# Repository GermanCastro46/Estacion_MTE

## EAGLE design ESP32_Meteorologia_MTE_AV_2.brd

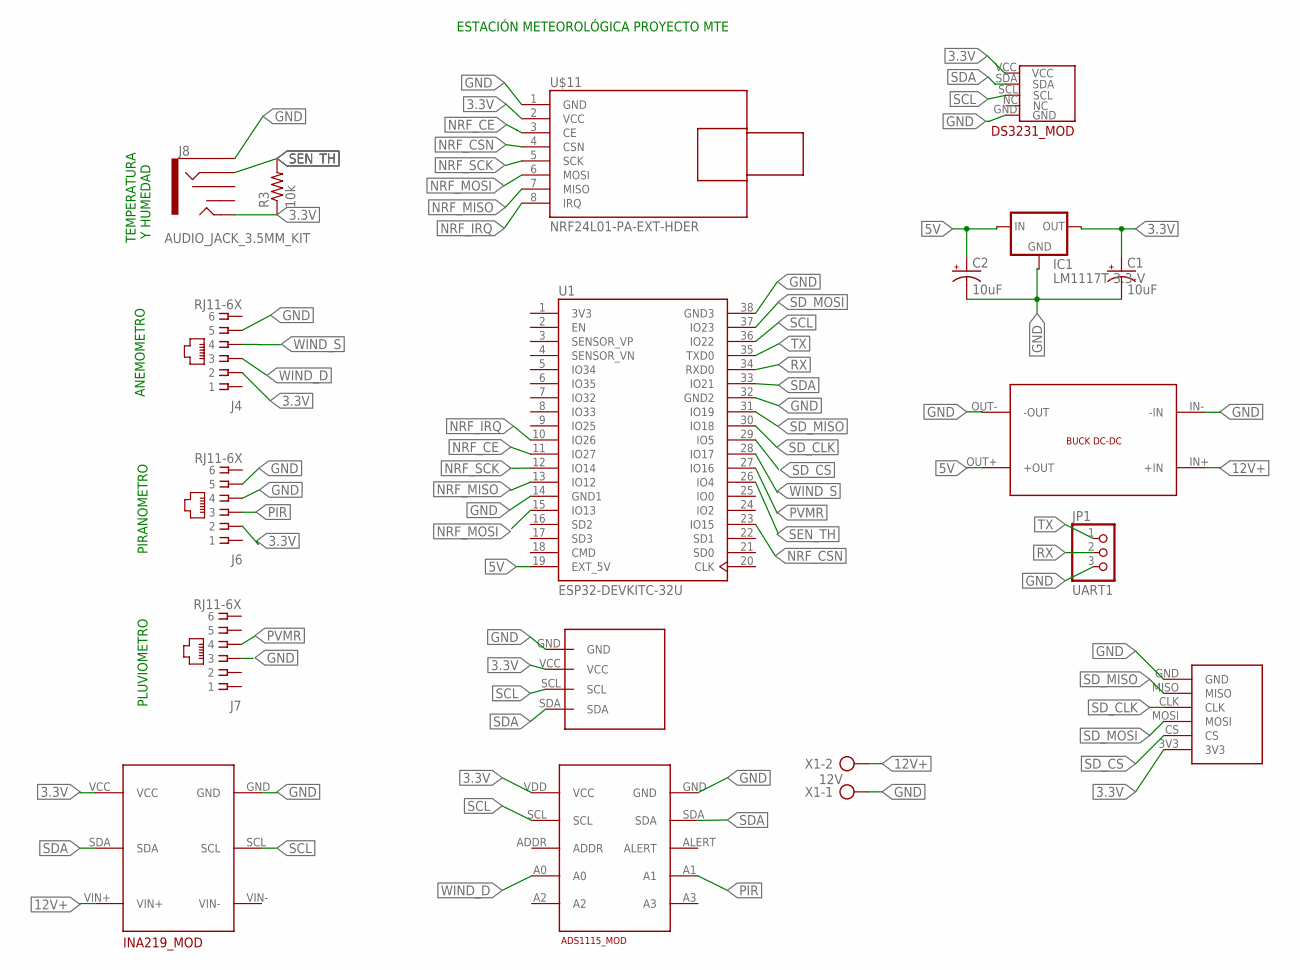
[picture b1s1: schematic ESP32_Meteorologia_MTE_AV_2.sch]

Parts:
C1, C2: 10uF; CPOL-RADIAL-2.5MM-5MM
IC1: LM1117T-3.3-V; TO220V
J4, J6, J7: RJ11-6X; RJ11-NO_SHIELD
J8: AUDIO_JACK_3.5MM_KIT; AUDIO-JACK-KIT
JP1: UART1; 1X03
R3: 10k; 0207/10
U1: ESP32-DEVKITC-32U; MODULE_ESP32-DEVKITC-32U
U$1: ADS1115_BIG
U$2: MODULO_MSD2; MICROSD-BREAKOUT
U$7: INA219_MOD_HDR
U$8: BUCK_LM2596
U$10: DS3231_MOD
U$11: NRF24L01-PA-EXT-HDER; NRF24L01-HEADER
U$12: OLED_I2C_096; OLED_096_I2C
X1: 12V; AK500/2

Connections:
3.3V: C1.1 (+), IC1.2 (OUT), J4.2, J6.2, J8.TIP, R3.1, U$1.VDD (VCC), U$2.3V3, U$7.VCC, U$10.VCC, U$11.2 (VCC), U$12.VCC
3V3: U1.1 (3V3)
5V: C2.1 (+), IC1.3 (IN), U1.19 (EXT_5V), U$8.OUT+ (+OUT)
12V+: U$7.VIN+, U$8.IN+ (+IN), X1.2
GND: C1.2 (-), C2.2 (-), IC1.1 (GND), J4.5, J6.4, J6.5, J7.3, J8.SLEEVE, JP1.3, U1.14 (GND1), U1.32 (GND2), U1.38 (GND3), U$1.GND, U$2.GND, U$7.GND, U$8.IN- (-IN), U$8.OUT- (-OUT), U$10.GND, U$11.1 (GND), U$12.GND, X1.1
NRF_CE: U1.11 (IO27), U$11.3 (CE)
NRF_CSN: U1.23 (IO15), U$11.4 (CSN)
NRF_IRQ: U1.10 (IO26), U$11.8 (IRQ)
NRF_MISO: U1.13 (IO12), U$11.7 (MISO)
NRF_MOSI: U1.15 (IO13), U$11.6 (MOSI)
NRF_SCK: U1.12 (IO14), U$11.5 (SCK)
PIR: J6.3, U$1.A1
PVMR: J7.4, U1.27 (IO16)
RX: JP1.2, U1.34 (RXD0)
SCL: U1.36 (IO22), U$1.SCL, U$7.SCL, U$10.SCL, U$12.SCL
SDA: U1.33 (IO21), U$1.SDA, U$7.SDA, U$10.SDA, U$12.SDA
SD_CLK: U1.30 (IO18), U$2.CLK
SD_CS: U1.29 (IO5), U$2.CS
SD_MISO: U1.31 (IO19), U$2.MISO
SD_MOSI: U1.37 (IO23), U$2.MOSI
SEN_TH: J8.RING, R3.2, U1.26 (IO4)
TX: JP1.1, U1.35 (TXD0)
WIND_D: J4.3, U$1.A0
WIND_S: J4.4, U1.28 (IO17)

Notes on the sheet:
ESTACIÓN METEOROLÓGICA PROYECTO MTE
ANEMOMETRO
PIRANOMETRO
PLUVIOMETRO
TEMPERATURA Y HUMEDAD

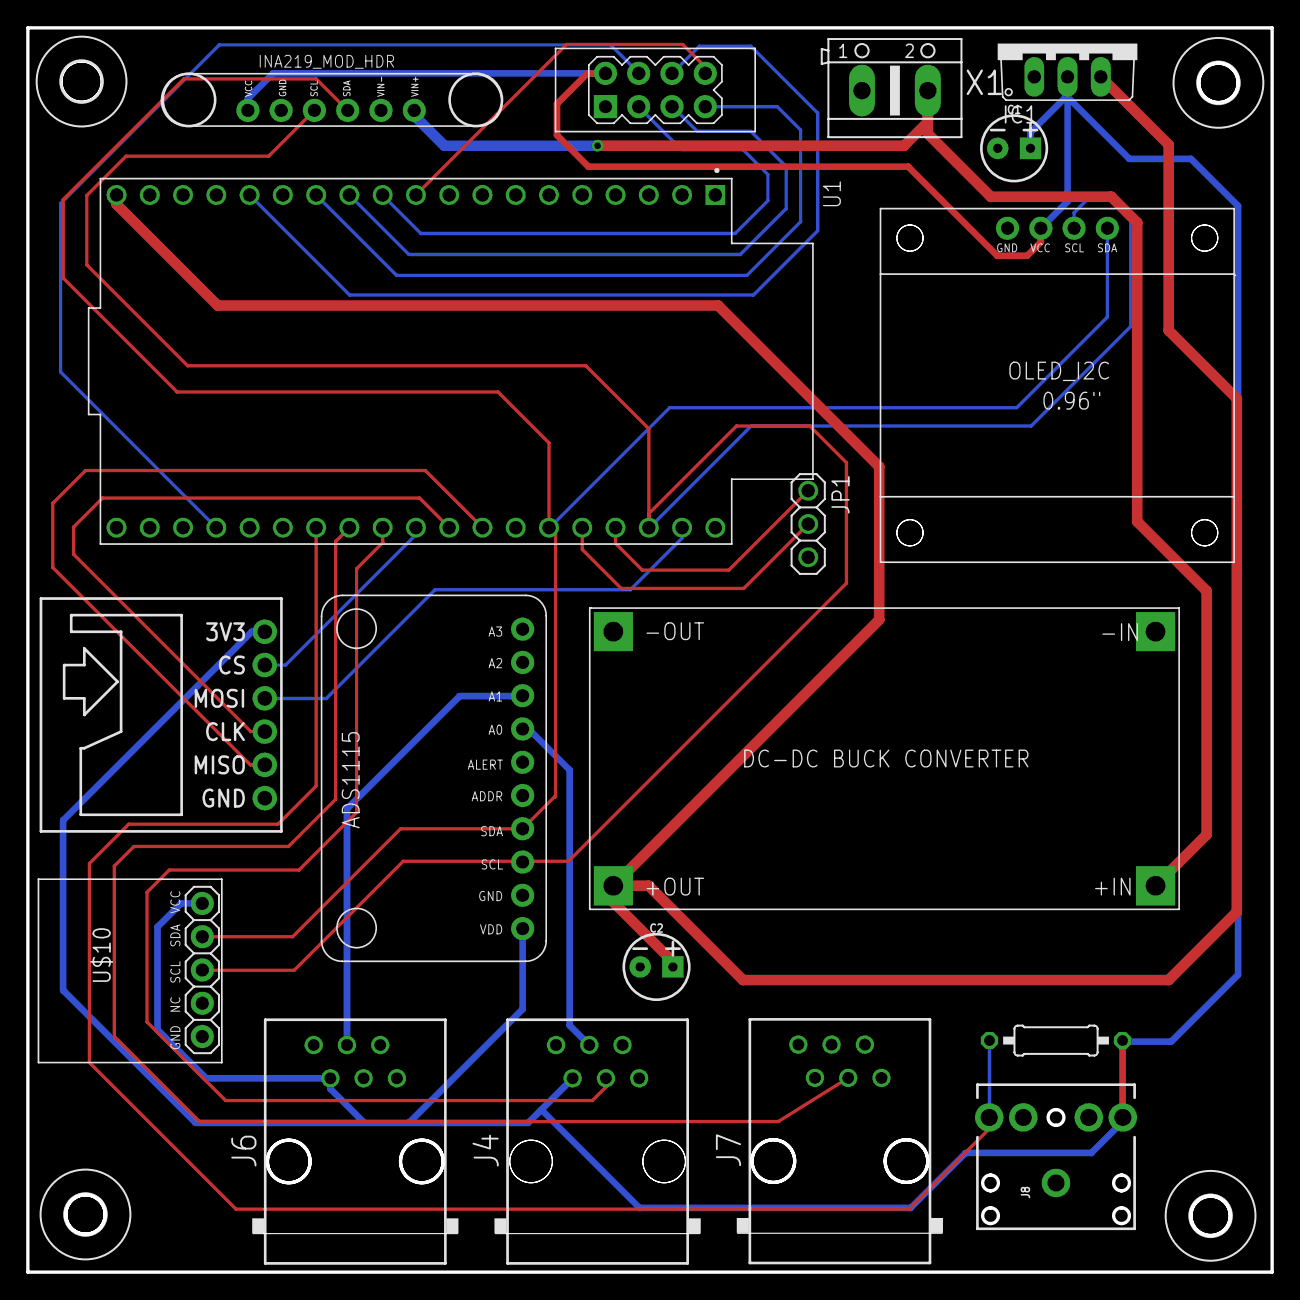
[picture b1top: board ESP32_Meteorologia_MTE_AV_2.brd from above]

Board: 2 copper layers, 95.0 x 95.0 mm, 22 parts (0 on the bottom side), 23 nets.

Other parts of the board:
U$3, U$4, U$5, U$6: 3,0

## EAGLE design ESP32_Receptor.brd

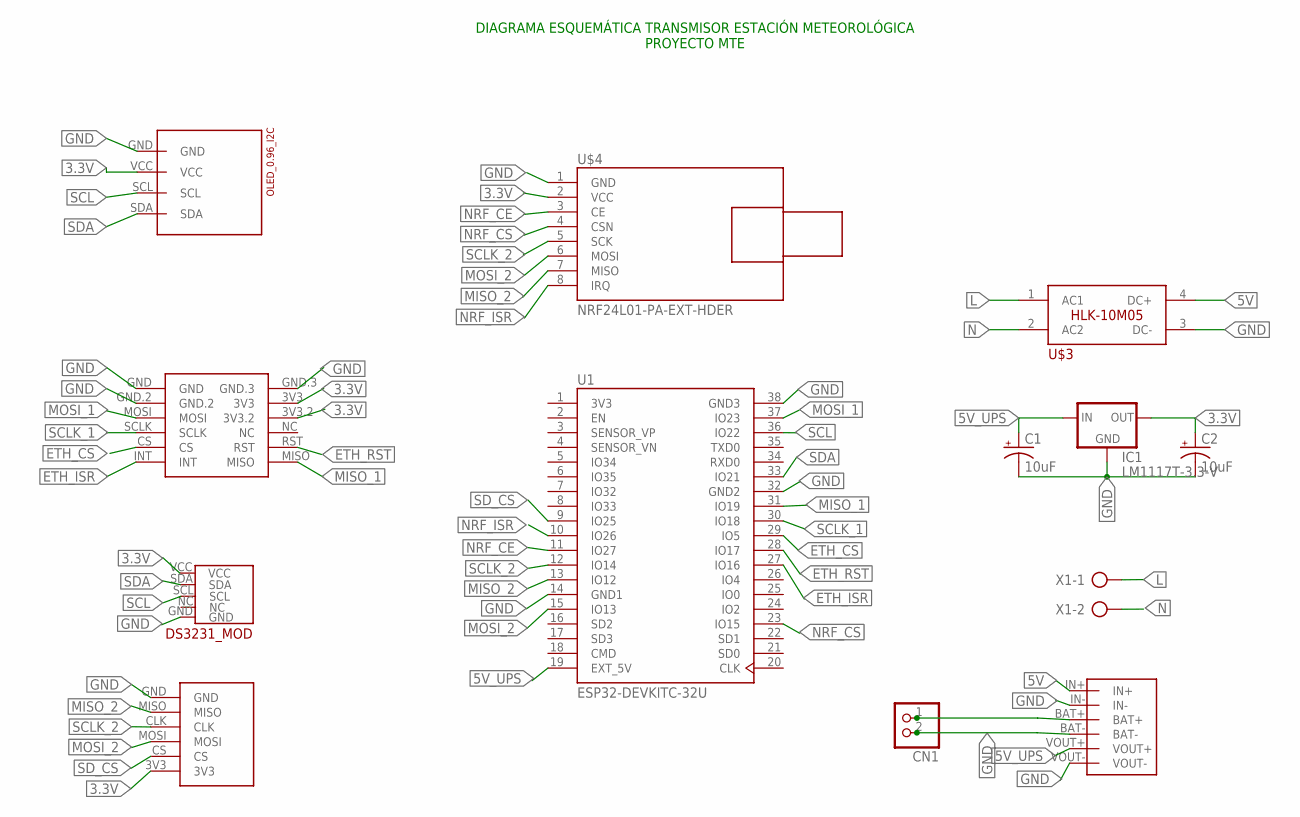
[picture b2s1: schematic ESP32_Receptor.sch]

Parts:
C1, C2: 10uF; CPOL-RADIAL-2.5MM-5MM
CN1: JST_2PIN-THM; JST-PH-2-THM
IC1: LM1117T-3.3-V; TO220V
U1: ESP32-DEVKITC-32U; MODULE_ESP32-DEVKITC-32U
U$1: MINI_W5500
U$2: DS3231_MOD
U$3: HLK-10M05
U$4: NRF24L01-PA-EXT-HDER; NRF24L01-HEADER
U$5: OLED_I2C_096; OLED_096_I2C
U$6: MODULO_MSD2; MICROSD-BREAKOUT
U$7: J5019_UPS
X1: AK500/2-H

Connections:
3.3V: C2.1 (+), IC1.2 (OUT), U$1.3V3, U$1.3V3.2, U$2.VCC, U$4.2 (VCC), U$5.VCC, U$6.3V3
3V3: U1.1 (3V3)
5V: U$3.4 (DC+), U$7.IN+
5V_UPS: C1.1 (+), IC1.3 (IN), U1.19 (EXT_5V), U$7.VOUT+
ETH_CS: U1.29 (IO5), U$1.CS
ETH_ISR: U1.27 (IO16), U$1.INT
ETH_RST: U1.28 (IO17), U$1.RST
GND: C1.2 (-), C2.2 (-), CN1.2 (1), IC1.1 (GND), U1.14 (GND1), U1.32 (GND2), U1.38 (GND3), U$1.GND, U$1.GND.2, U$1.GND.3, U$2.GND, U$3.3 (DC-), U$4.1 (GND), U$5.GND, U$6.GND, U$7.BAT-, U$7.IN-, U$7.VOUT-
L: U$3.1 (AC1), X1.1
MISO_1: U1.31 (IO19), U$1.MISO
MISO_2: U1.13 (IO12), U$4.7 (MISO), U$6.MISO
MOSI_1: U1.37 (IO23), U$1.MOSI
MOSI_2: U1.15 (IO13), U$4.6 (MOSI), U$6.MOSI
N: U$3.2 (AC2), X1.2
unnamed: CN1.1 (2), U$7.BAT+
NRF_CE: U1.11 (IO27), U$4.3 (CE)
NRF_CS: U1.23 (IO15), U$4.4 (CSN)
NRF_ISR: U1.10 (IO26), U$4.8 (IRQ)
SCL: U1.36 (IO22), U$2.SCL, U$5.SCL
SCLK_1: U1.30 (IO18), U$1.SCLK
SCLK_2: U1.12 (IO14), U$4.5 (SCK), U$6.CLK
SDA: U1.33 (IO21), U$2.SDA, U$5.SDA
SD_CS: U1.9 (IO25), U$6.CS

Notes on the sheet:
DIAGRAMA ESQUEMÁTICA TRANSMISOR ESTACIÓN METEOROLÓGICA PROYECTO MTE

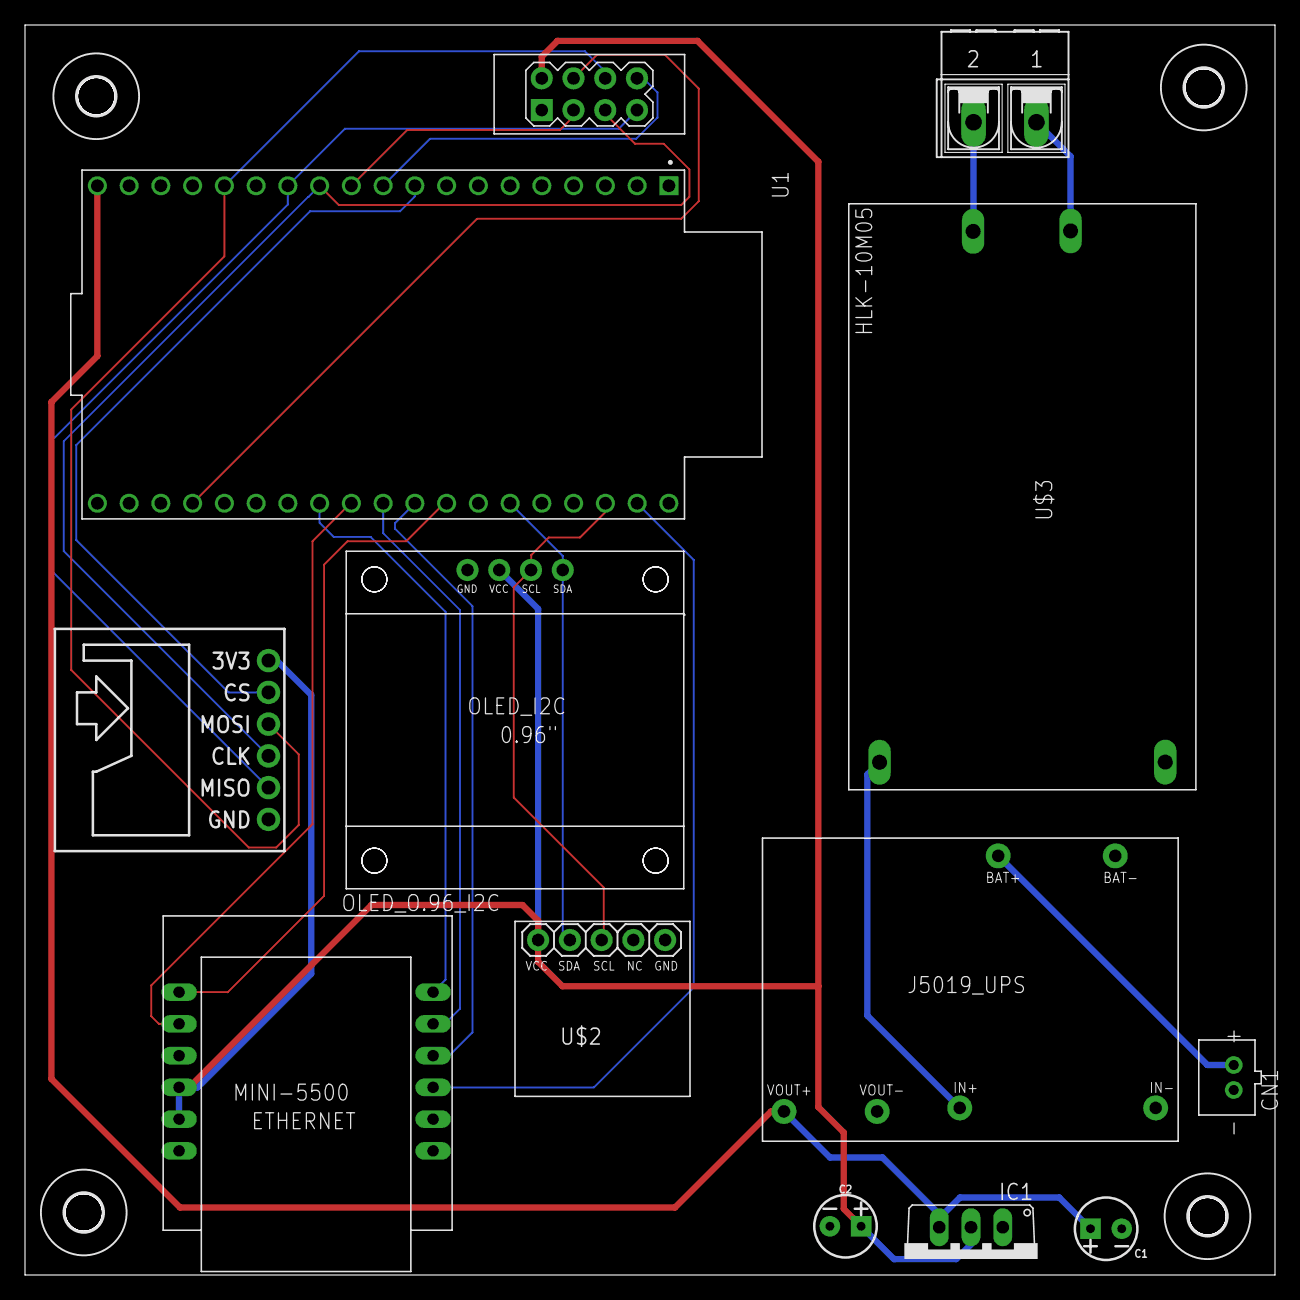
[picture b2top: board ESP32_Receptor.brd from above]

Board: 2 copper layers, 100.0 x 100.0 mm, 17 parts (0 on the bottom side), 22 nets.

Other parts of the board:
U$8, U$9, U$10, U$11: 3,0

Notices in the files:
parts and their libraries:
SparkFun-Connectors: Licensing: Creative Commons ShareAlike 4.0 International - https://creativecommons.org/licenses/by-sa/4.0
